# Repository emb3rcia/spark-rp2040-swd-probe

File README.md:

# spark-rp2040-swd-probe

> [!WARNING]
> This project is under active development. Firmware is not started.
> Currently, board is not confirmed to be working nor yet manufactured

# Navigation

- [About the project](#about-the-project)
  - [Motivation](#motivation)
  - [Usage](#usage)
  - [Directory overview](#directory-overview)
  - [Development tools](#development-tools)
  - [Features](#features)
- [Images](#images)
- [License](#license)
- [AI declaration](#ai-declaration)

# About the project

spark-rp2040-swd-probe is SWD probe with support for SWO, as well as BOOT_SEL support incoming via add-on board, based on Raspberry Pi Foundation's `debug-probe` firmware.

## Motivation

I wanted to make cheap, open source and readily available version of SWD probes available commercialy, but with level shifters, LEDs etc.

## Usage

Firmware implementation as well as software support isn't yet done or verified.

## Directory overview

- `/Firmware` - adapted `debug-probe` firmware (PLANNED)
- `/PCB` - editable KiCad project
- `/Gerbers` - generated PCB fabrication files
- `/Images` - project images and renders
- `/Licenses` - license texts
- `/Schematic` - schematic PDF (via KiCad plot feature)

## Development tools

- KiCad for EDA work
- Visual Studio Code for firmware adaptation
- FreeCAD for enclosures

## Features

- SWO capture
- Level shifters down to 1V2 (1.2V)
- Status and activity LEDs
- Target connected LED
- Target voltage LED

# Images

Front

# License

This repository contains material under multiple licenses. Individual file-level notices and third-party licenses take precedence over these directory-level defaults.

## Hardware license

Original files under `/PCB`, `/Schematic` and `/Gerbers` are licensed under the CERN Open
Hardware Licence Version 2 – Weakly Reciprocal.

See `/Licenses/CERN-OHL-W-2.0.txt` for full terms.

## Firmware license

Original files under `/Firmware` are licensed under the Apache License 2.0.

See `/Licenses/Apache-2.0.txt` for full terms.

## Documentation and media

The root `README.md`, and original images,
renders, and photographs under `/Images` are licensed under the Creative Commons Attribution 4.0 International license.

See `/Licenses/CC-BY-4.0.txt` for full terms.

Only material owned by the project is covered. Third-party assets retain their original licenses.

Project names, logos, and wordmarks are not licensed unless explicitly stated.

# AI Declaration

ChatGPT was used in process of making this project.

Uses of it include debugging help, datasheet key information extraction, validation of code and others.

© 2026 emb3rcia

- Firmware: Apache-2.0
- Hardware and manufacturable CAD: CERN-OHL-W-2.0
- Documentation and original media: CC-BY-4.0

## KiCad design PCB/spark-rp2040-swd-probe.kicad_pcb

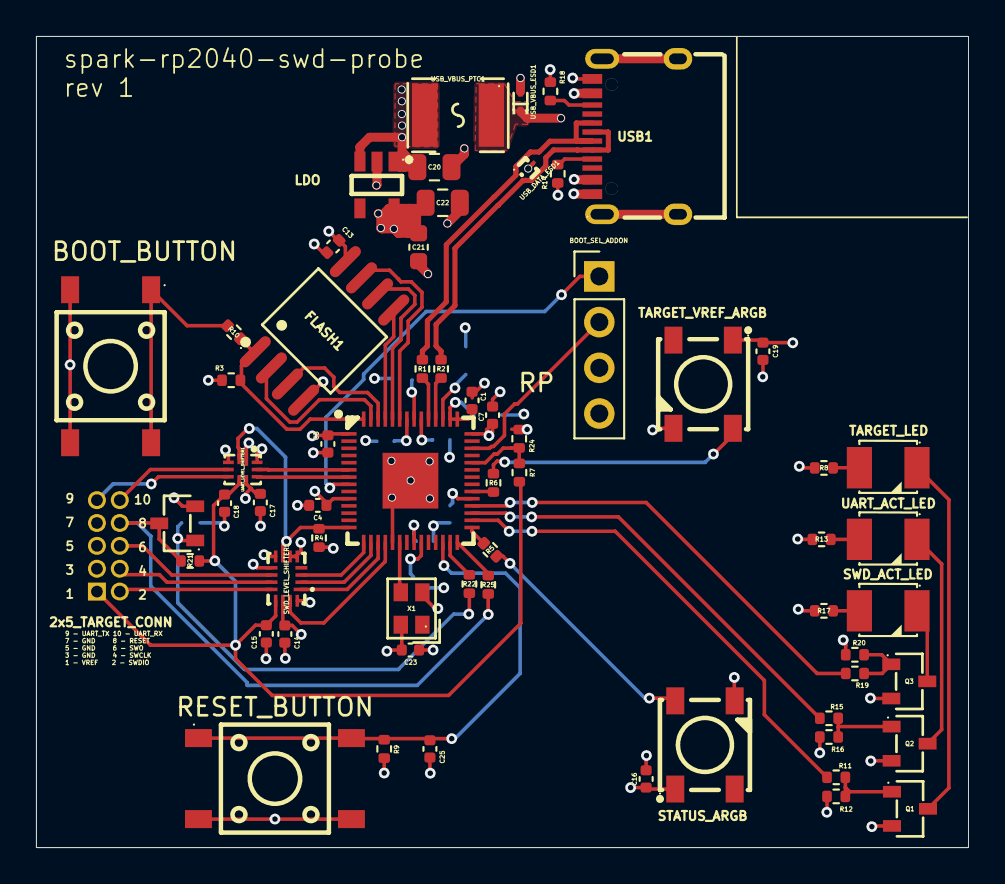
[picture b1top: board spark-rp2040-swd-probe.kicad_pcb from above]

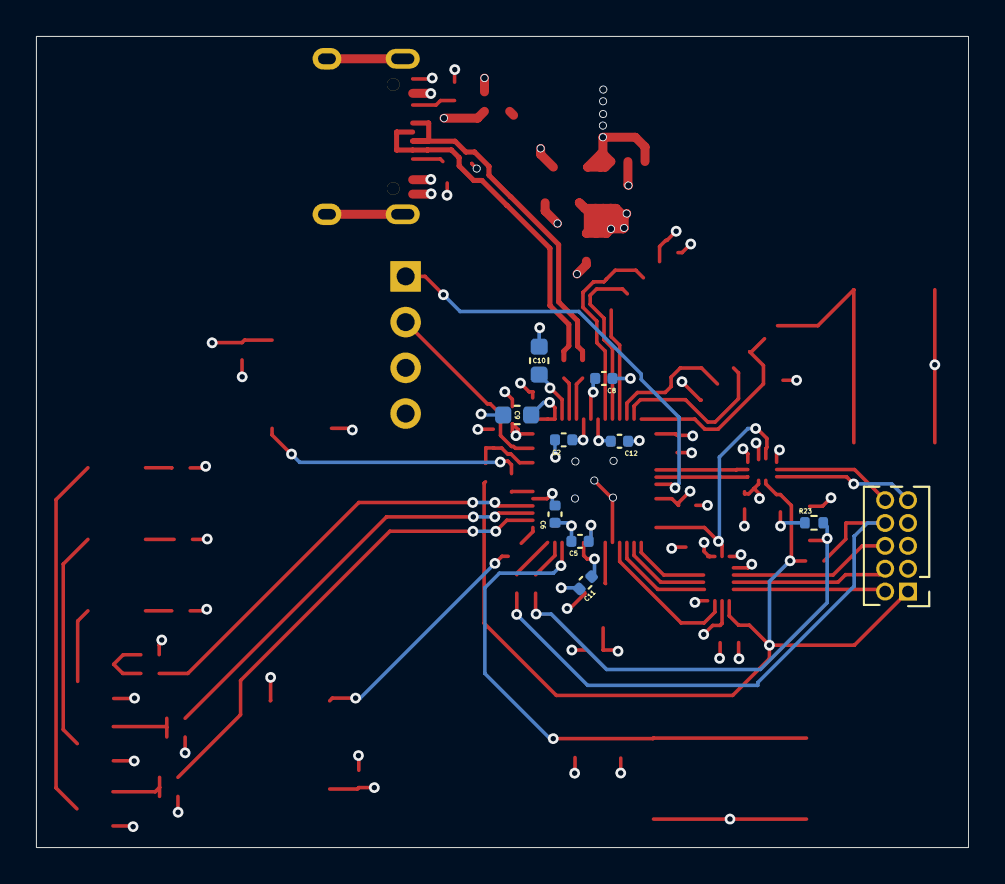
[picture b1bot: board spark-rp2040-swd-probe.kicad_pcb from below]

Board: 4 copper layers, 51.8 x 45.1 mm, 72 parts (10 on the bottom side), 56 nets.

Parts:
2x5_TARGET_CONN: Conn_02x05_Counter_Clockwise; PinHeader_2x05_P1.27mm_Vertical
BOOT_BUTTON: TS6643TP 250GF 009; SW-SMD_4P-L6.2-W6.0-P4.50-LS9.0
BOOT_SEL_ADDON: Conn_01x04_Pin; PinHeader_1x04_P2.54mm_Vertical
C1, C2, C3, C4, C5, C6, C7, C8, C11, C12, C13, C14, C15, C16, C17, C18, C19, C23, C25: 100nF; C_0402_1005Metric
C9, C10, C21: 1uF; C_0603_1608Metric
C20: 1uF; C_0805_2012Metric
C22: 10uF; C_0805_2012Metric
FLASH1: GD25Q64ESIGR; SOP-8_L5.3-W5.3-P1.27-LS7.9-BL
LDO: AP2112K-3.3TRG1; SOT-25-5_L2.9-W1.6-P0.95-LS2.8-BL
Q1, Q2, Q3: 2N7002_C916396; SOT-23-3_L2.9-W1.3-P1.90-LS2.4-BR
R1, R2: 27Ohm; R_0402_1005Metric
R3, R4, R9, R21, R25: 10kOhm; R_0402_1005Metric
R5, R6: 33Ohm; R_0402_1005Metric
R7, R12, R16, R20, R23, R24: 100kOhm; R_0402_1005Metric
R8, R10, R13, R17, R22: 1kOhm; R_0402_1005Metric
R11, R15, R19: 100Ohm; R_0402_1005Metric
R14, R18: 5.1kOhm; R_0402_1005Metric
RESET_BUTTON: TS6643TP 250GF 009; SW-SMD_4P-L6.2-W6.0-P4.50-LS9.0
RP: RP2040; LQFN-56_L7.0-W7.0-P0.4-EP
STATUS_ARGB: WS2812B-B-V6; LED-SMD_4P-L5.0-W5.0-TL_WS2812B-B
SWD_ACT_LED: XL-3528UWC; LED-SMD_L3.2-W2.8-LS3.5-XL-3528SURC
SWD_LEVEL_SHIFTER1: SN74AXC4T774RSVR; UQFN-16_L2.6-W1.8-P0.40-BL
TARGET_LED: XL-3528UWC; LED-SMD_L3.2-W2.8-LS3.5-XL-3528SURC
TARGET_RESET_NMOS1: 2N7002_C916396; SOT-23-3_L2.9-W1.3-P1.90-LS2.4-BR
TARGET_VREF_ARGB: WS2812B-B-V6; LED-SMD_4P-L5.0-W5.0-TL_WS2812B-B
UART_ACT_LED: XL-3528UWC; LED-SMD_L3.2-W2.8-LS3.5-XL-3528SURC
UART_LEVEL_SHIFTER1: SN74AXC2T245RSWR; UQFN-10_L1.8-W1.4-P0.40-TL
USB1: TYPE-C 16PIN 2MD; USB-C-SMD_TYPE-C-16PIN-2MD-073
USB_DATA_ESD1: TPD2EUSB30ADRTR; SOT-9X3-3_L1.0-W0.8-P0.35-LS1.0-BR
USB_VBUS_ESD1: ESD9L5.0ST5G; SOD-923_L0.8-W0.6-LS1.0-RD
USB_VBUS_PTC1: MINISMDC050F-2; F1812
X1: SX1M12.000M10F30TNN; OSC-SMD_4P-L2.0-W1.6-BL

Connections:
3V3: BOOT_SEL_ADDON.3, C1.1, C2.1, C3.1, C4.1, C5.1, C6.1, C7.1, C8.1, C9.1, C13.1, C14.1, C16.1, C17.1, C19.1, C21.1, C22.1, C23.1, FLASH1.8 (VCC), LDO.5 (VOUT), R3.1, R4.1, R9.1, RP.1 (IOVDD), RP.10 (IOVDD), RP.22 (IOVDD), RP.33 (IOVDD), RP.42 (IOVDD), RP.43 (ADC_AVDD), RP.44 (VREG_IN), RP.48 (USB_VDD), RP.49 (IOVDD), STATUS_ARGB.1 (VDD), SWD_LEVEL_SHIFTER1.14 (VCCA), SWD_LEVEL_SHIFTER1.16 (DIR2), TARGET_VREF_ARGB.1 (VDD), UART_LEVEL_SHIFTER1.1 (DIR2), UART_LEVEL_SHIFTER1.7 (VCCA), X1.4 (VDD)
5V: C20.1, LDO.1 (VIN), LDO.3 (EN), R8.1, R13.1, R17.1, USB_VBUS_PTC1.2
BOOT_SEL_TARGET: BOOT_SEL_ADDON.1, RP.8 (GPIO6)
BOOT_SEL_TARGET_VREF: BOOT_SEL_ADDON.2, RP.40 (GPIO28_ADC2)
D+: R1.2, USB1.A6 (Dp1), USB1.B6 (Dp2), USB_DATA_ESD1.1 (D+)
D-: R2.2, USB1.A7 (Dn1), USB1.B7 (Dn2), USB_DATA_ESD1.2 (D-)
FLASH_CS: FLASH1.1 (~CS), R3.2, R10.1, RP.56 (QSPI_SS)
FLASH_SCLK: FLASH1.6 (SCLK), RP.52 (QSPI_SCLK)
FLASH_SD0: FLASH1.5 (SI(IO0)), RP.53 (QSPI_SD0)
FLASH_SD1: FLASH1.2 (SO(IO1)), RP.55 (QSPI_SD1)
FLASH_SD2: FLASH1.3 (WP#(IO2)), RP.54 (QSPI_SD2)
FLASH_SD3: FLASH1.7 (HOLD#(IO3)), RP.51 (QSPI_SD3)
GND: 2x5_TARGET_CONN.3, 2x5_TARGET_CONN.5, 2x5_TARGET_CONN.7, BOOT_BUTTON.3 (C), BOOT_BUTTON.4 (D), BOOT_SEL_ADDON.4, C1.2, C2.2, C3.2, C4.2, C5.2, C6.2, C7.2, C8.2, C9.2, C10.2, C11.2, C12.2, C13.2, C14.2, C15.2, C16.2, C17.2, C18.2, C19.2, C20.2, C21.2, C22.2, C23.2, C25.2, FLASH1.4 (VSS), LDO.2 (GND), Q1.2 (S), Q2.2 (S), Q3.2 (S), R12.1, R14.2, R16.1, R18.2, R20.1, R23.1, R24.2, RESET_BUTTON.3 (C), RESET_BUTTON.4 (D), RP.19 (TESTEN), RP.57 (GND), STATUS_ARGB.3 (VSS), SWD_LEVEL_SHIFTER1.5 (DIR3), SWD_LEVEL_SHIFTER1.6 (DIR4), SWD_LEVEL_SHIFTER1.8 (GND), TARGET_RESET_NMOS1.2 (S), TARGET_VREF_ARGB.3 (VSS), UART_LEVEL_SHIFTER1.3 (GND), UART_LEVEL_SHIFTER1.10 (DIR1), USB1.13 (EH), USB1.14 (EH), USB1.A1B12 (GND), USB1.B1A12 (GND), USB_DATA_ESD1.3 (GND), USB_VBUS_ESD1.2 (A), X1.2 (GND)
LED_SWD_ACT: R19.2, RP.32 (GPIO21)
LED_TARGET: R11.2, RP.30 (GPIO19)
LED_UART_ACT: R15.2, RP.31 (GPIO20)
unnamed: BOOT_BUTTON.1 (A), BOOT_BUTTON.2 (B), R10.2
unnamed: Q1.3 (D), TARGET_LED.1 (-)
unnamed: Q1.1 (G), R11.1, R12.2
unnamed: Q2.3 (D), UART_ACT_LED.1 (-)
unnamed: Q2.1 (G), R15.1, R16.2
unnamed: Q3.3 (D), SWD_ACT_LED.1 (-)
unnamed: Q3.1 (G), R19.1, R20.2
unnamed: R7.2, R24.1, RP.38 (GPIO26_ADC0)
unnamed: R2.1, RP.46 (USB_DM)
unnamed: R1.1, RP.47 (USB_DP)
unnamed: C10.1, C11.1, C12.1, RP.23 (DVDD), RP.45 (VREG_VOUT), RP.50 (DVDD)
unnamed: R5.1, STATUS_ARGB.4 (DIN)
unnamed: R17.2, SWD_ACT_LED.2 (+)
unnamed: R8.2, TARGET_LED.2 (+)
unnamed: R22.2, R23.2, TARGET_RESET_NMOS1.1 (G)
unnamed: R6.1, TARGET_VREF_ARGB.4 (DIN)
unnamed: R13.2, UART_ACT_LED.2 (+)
unnamed: R14.1, USB1.A5 (CC1)
unnamed: R18.1, USB1.B5 (CC2)
RGB_LED_STATUS: R5.2, RP.29 (GPIO18)
RGB_LED_TARGET: R6.2, RP.34 (GPIO22)
SWCLK_A: RP.16 (GPIO13), SWD_LEVEL_SHIFTER1.2 (A2)
SWDIO_A: RP.17 (GPIO14), SWD_LEVEL_SHIFTER1.1 (A1)
SWD_DIR: RP.18 (GPIO15), SWD_LEVEL_SHIFTER1.15 (DIR1)
SWO_A: RP.15 (GPIO12), SWD_LEVEL_SHIFTER1.3 (A3)
TARGET_RESET: 2x5_TARGET_CONN.8, R21.2, R25.1, TARGET_RESET_NMOS1.3 (D)
TARGET_RESET_CTRL: R22.1, RP.27 (GPIO16)
TARGET_RESET_SENSE: R25.2, RP.28 (GPIO17)
TARGET_SWCLK: 2x5_TARGET_CONN.4, SWD_LEVEL_SHIFTER1.11 (B2)
TARGET_SWDIO: 2x5_TARGET_CONN.2, SWD_LEVEL_SHIFTER1.12 (B1)
TARGET_SWO: 2x5_TARGET_CONN.6, SWD_LEVEL_SHIFTER1.10 (B3)
TARGET_UART_RX: 2x5_TARGET_CONN.10, UART_LEVEL_SHIFTER1.4 (B2)
TARGET_UART_TX: 2x5_TARGET_CONN.9, UART_LEVEL_SHIFTER1.5 (B1)
TARGET_VREF: 2x5_TARGET_CONN.1, C15.1, C18.1, R7.1, R21.1, SWD_LEVEL_SHIFTER1.13 (VCCB), UART_LEVEL_SHIFTER1.6 (VCCB)
TRANSLATOR_OE_N: R4.2, RP.14 (GPIO11), SWD_LEVEL_SHIFTER1.7 (~OE), UART_LEVEL_SHIFTER1.2 (~OE)
UART_RX_A: RP.7 (GPIO5), UART_LEVEL_SHIFTER1.8 (A1)
UART_TX_A: RP.6 (GPIO4), UART_LEVEL_SHIFTER1.9 (A2)
VBUS: USB1.A4B9 (VBUS), USB1.B4A9 (VBUS), USB_VBUS_ESD1.1 (C), USB_VBUS_PTC1.1
XIN: RP.20 (XIN), X1.3 (OUT)
nRESET: C25.1, R9.2, RESET_BUTTON.1 (A), RESET_BUTTON.2 (B), RP.26 (RUN)
